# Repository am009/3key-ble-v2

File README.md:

# 3-key-ble-v2

Tiny 3-key ble keyboard. Based on https://github.com/Xinyuan-LilyGO/LilyGo-T-OI-PLUS

基于https://github.com/Xinyuan-LilyGO/LilyGo-T-OI-PLUS 画简单的拓展板，满足自己3键蓝牙键盘需求。通过排针排母连接

### feature

- kailh hotswap sockets
- simple pcb, simple code, easy to understand

### photos

### 笔记

https://github.com/espressif/arduino-esp32 首先搞一下开发环境。https://docs.espressif.com/projects/arduino-esp32/en/latest/getting_started.html 这里跟着做一下。

https://github.com/wakwak-koba/ESP32-NimBLE-Keyboard 这人改装了一下。但是原来的库：https://github.com/T-vK/ESP32-BLE-Keyboard 这个已经merge了那个NimBLE库的支持，只需要启用一下。那我直接用就可以了应该。

【！！】解决按键上拉的问题：https://github.com/espressif/arduino-esp32/discussions/6197 c3不支持captive touch怎么办。。。pcb上加上拉电阻吧。

https://www.reddit.com/r/olkb/comments/ckbprk/kicad_footprint_for_kaihl_hotswap_socket_and/ 这个人说https://github.com/ai03-2725/MX_Alps_Hybrid 有hotswap sockets。https://github.com/perigoso/keyswitch-kicad-library 这里发现也有。用这个了。直接Plugin and Content Manager在KiCAD里面直接下载。

https://www.bookstack.cn/read/kicad-5.1.5-zh/OEBPS-ch05s04.html KiCAD的中文教程书

https://haipeng.me/2017/03/01/kicad-tutorial/ 另一个完整的教程

### 电路板

安装Kicad先，然后先选择引脚，画原理图。正反千万别弄错。

引脚选择看：https://docs.espressif.com/projects/esp-idf/zh_CN/latest/esp32c3/api-reference/peripherals/gpio.html 

其中Strapping pin好像是和开机启动进入不同模式有关。可以考虑避开。好像有些要求所以板子其实有对IO8上拉。但是查了下NC表示空贴，意思是其他的都空贴了。仔细观察了一下，看了半天，确实有5个空的电阻位子。看来上拉电阻一般都用10k。然后我也默认上拉，按下按钮的时候被下拉。

RTC应该不用管，我直接开关断电还是最好的。

最终选择的IO：GPIO 4、6、7

### 创建元件

创建TOI-plus的元件symbol和footprint。应该是配套的库，一个是原理图上的，一个是PCB上的。

google搜索kicad add project specific symbol，我参考的是https://www.protoexpress.com/blog/how-to-create-a-schematic-and-symbol-library-kicad/ 

unit好像指的是一个symbol分很多不同部件。所以应该不用管，选1。然后注意观察其他的元件是怎么画的，画一个框然后放好点位就可以了。为了方便后面map到排母的footprint，分两个symbol画。不要分两个unit（因为好像只能一个symbol map一个footprint）。

下载的时候那个键盘库只有footprint。所以原理图就用SW_Push简单的按钮代替。

上拉参考下面的这个。贴片电阻map的时候暂时选用0603。

无语，安装了结果路径没有加到footprint库。还得我手动加。"C:\Users\xxx\Documents\KiCad\6.0\3rdparty\footprints\com_github_perigoso_keyswitch-kicad-library\Switch_Keyboard_Hotswap_Kailh.pretty"

plated后缀的区别在于：https://www.pcbunlimited.com/engineering/plated-non-plated-through-holes NPTH的洞和PTH的洞。其实就是看你要不要洞里带焊锡。那还是带着吧。好像是PTH是正常的过孔，不需要额外收费的。

### PCB

原理图搞正确后直接选tools update from schematic就直接出来元件和指示线了。

加的测量线的名字叫dimension。摆好元件后就可以

嘉立创的注意事项在https://www.jlc.com/portal/vtechnology.html 然后到net class里可以改。用默认值就可以。

https://blog.csdn.net/qq_52940987/article/details/124570167 选择线宽线距

https://www.cnblogs.com/F4NNIU/p/10495105.html 画板框

创建了覆铜区域之后铜没上去，右键点zone->fill zone才覆上去了。

最小字符宽6mil=0.1524mm，字符高40mil=1.016mm。还说是极限值。。

https://www.jlc.com/portal/t6i403.html 嘉立创客户编号。算了，占掉靠外的位置，让他们随便加吧

https://www.chenxublog.com/2021/10/08/kicad-jlc-gerber.html 生成生产文件。

### 硬件购买

键盘轴，热拔插座，16340 3.7v电池，矮排针，贴片电阻，

量一下3d模型里面热拔插座的厚度，应该是顶在typec接口上面，防止插不进去甚至还要多留一点

下面留5.5mm，热拔插座1.85mm算1.9，typc母算3.5mm。那两PCB间考虑留5.5-6.5mm。排针塑高快2mm。。。那买3.5的和5的都来试试吧。最后发现3.5mm排针刚好合适，甚至还多有一点点位置。

最后翻车的两点：8pin排针买成了6pin。忘了买镊子。。。还好后面找到了个。0805贴片电阻还是有点难焊啊。注意焊接排针排母的时候，（焊完一边焊另一边的时候）考虑把整个（排针和排母）接起来再焊接，防止微小的公差导致对接的时候焊盘受力。

### 软件

为了按键防抖，30ms后采样。用最简单的方法ISR里去设置bool值为真，然后用死循环，如果那边bool变化了，就sleep 30ms后对对应的按键状态进行采样，然后更新一下BLE键盘的按键状态。突然发现example里面有个functional interrupt，写得非常清晰。

开发环境大概就是，安装arduino，然后根据教程安装esp32系列板子，然后安装ESP32-BLE-Keyboard库。最后记得启用里面的NimBLE mode，Uncomment the first line in BleKeyboard.h。

1.	实现一个按下按键串口打印的框架。
2.	对接蓝牙键盘库。
3.	处理电量指示。唯一有点复杂的地方：https://github.com/Xinyuan-LilyGO/LilyGo-T-OI-PLUS/issues/19 

最终代码在arduino/main/main.ino。非常简单。上次搞得太复杂了。

### 总结

第二次做有一些经验了，最早想自己完整设计板子的，无奈电池管理模块什么的还是太难了。

希望这次基于ESP32C3这个RISC-V的板子能够续航更长，热拔插键轴也更方便更换。屏幕果然完全不需要，还是省电比较重要，电池电量完全可以通过蓝牙在主机端显示

欢迎邮件交流。

上次的板子在：https://github.com/am009/my-3key-ble-keyboard

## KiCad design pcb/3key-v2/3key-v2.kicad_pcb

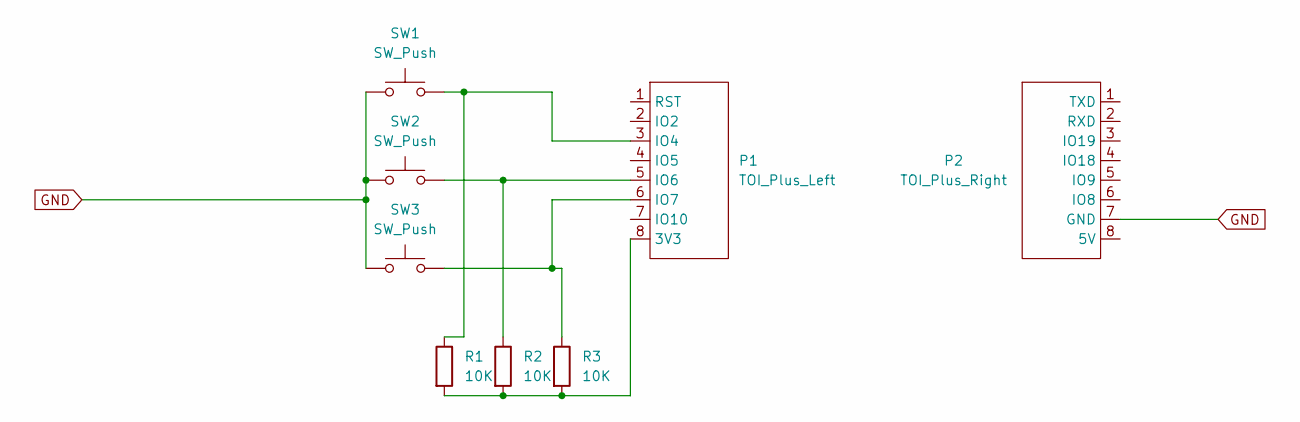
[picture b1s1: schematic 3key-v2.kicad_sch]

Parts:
P1: TOI_Plus_Left; PinSocket_1x08_P2.54mm_Vertical
P2: TOI_Plus_Right; PinSocket_1x08_P2.54mm_Vertical
R1, R2, R3: 10K; R_0805_2012Metric_Pad1.20x1.40mm_HandSolder
SW1, SW2, SW3: SW_Push; SW_Hotswap_Kailh_MX_plated_1.00u

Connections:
GND: P2.7 (GND), SW1.1, SW2.1, SW3.1
unnamed: P1.3 (IO4), R1.1, SW1.2
unnamed: P1.5 (IO6), R2.1, SW2.2
unnamed: P1.6 (IO7), R3.1, SW3.2
unnamed: P1.8 (3V3), R1.2, R2.2, R3.2

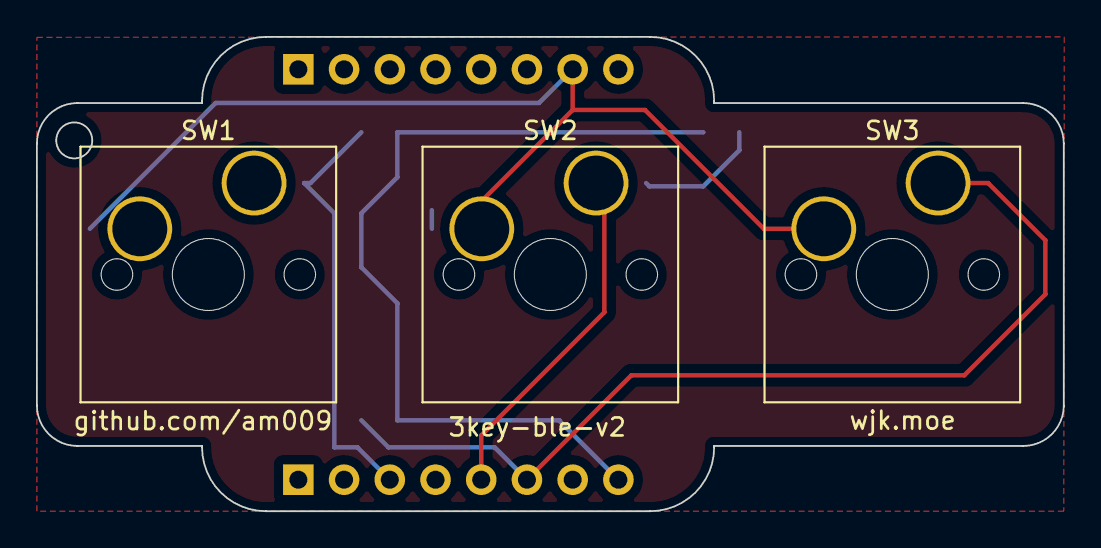
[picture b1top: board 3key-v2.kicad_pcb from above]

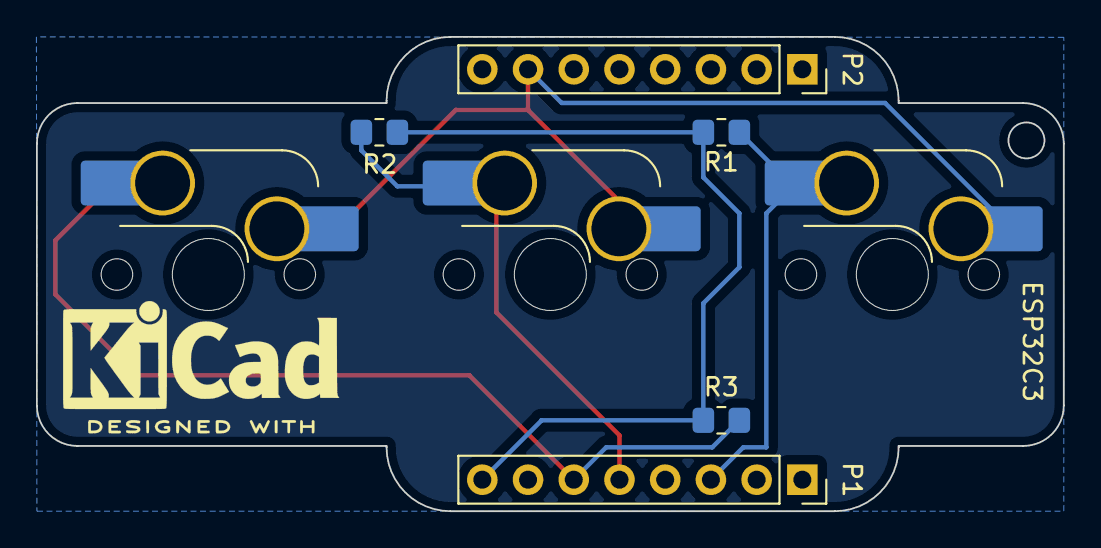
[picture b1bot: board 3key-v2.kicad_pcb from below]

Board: 2 copper layers, 57.1 x 26.3 mm, 8 parts (5 on the bottom side), 5 nets.

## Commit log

2022-05-28 Initial commit.
2022-05-28 Add README.md and images.
